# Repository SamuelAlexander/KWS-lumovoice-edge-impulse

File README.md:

# Lumo Voice

Lumo Voice is a keyword spotting (KWS) project utilizing the Arduino Nicla Voice platform, designed to control LED lighting. This repository includes:

- **Arduino Code**: Arduino code for the Nicla Voice.
- **KiCAD PCB Files**: Schematics and PCB design for the custom LED control PCB.
- **Manufacturing**: Gerber, drill, and SMD Bill of Materials

## Getting Started

1. **Firmware**: Upload the Arduino code to the Nicla Voice..
2. **Hardware**: Use the provided KiCAD files to manufacture the custom PCB.

## Usage

The device responds to voice commands "extinguish" and "illuminate" to control the lights. An "z_openset" category handles unrecognized commands.

## License

This project is licensed under the Apache 2.0 License - see the [LICENSE](LICENSE) file for details.

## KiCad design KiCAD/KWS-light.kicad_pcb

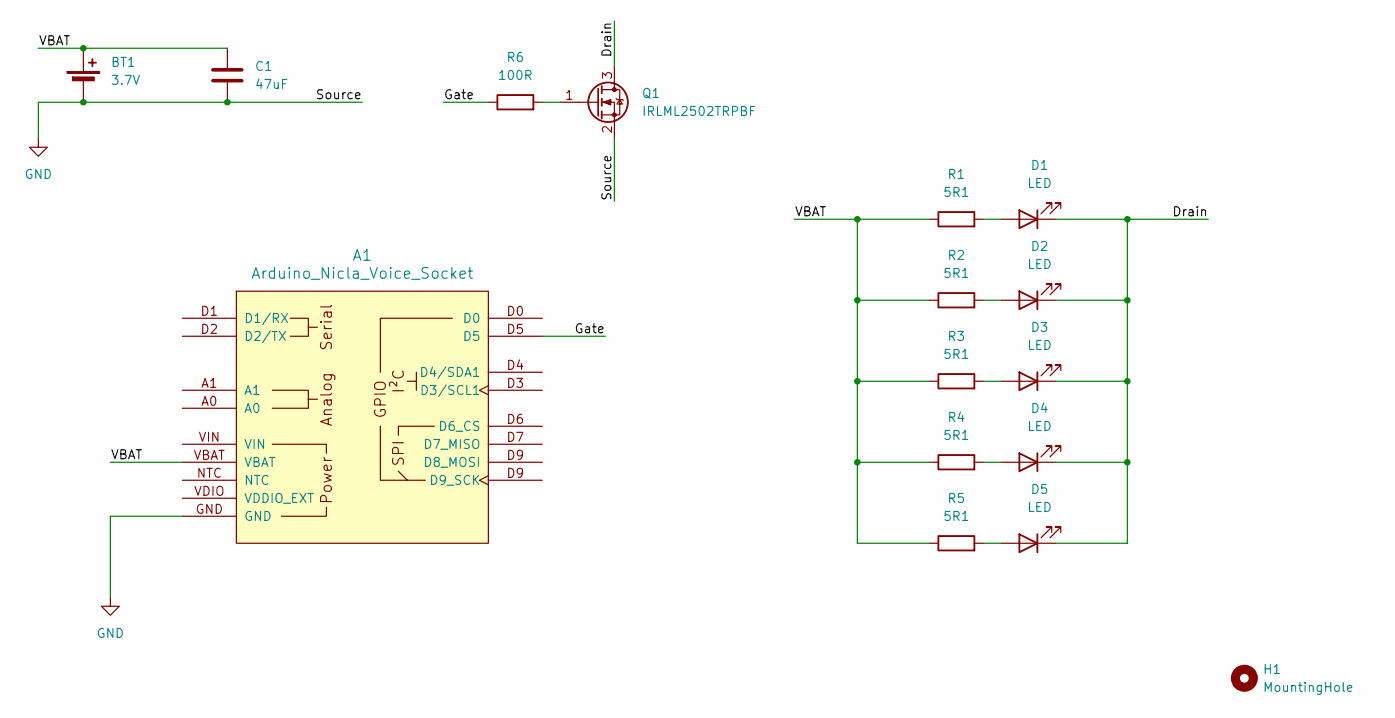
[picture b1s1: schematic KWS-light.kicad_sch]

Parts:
A1: Arduino_Nicla_Voice_Socket
BT1: 3.7V; PinSocket_1x02_P2.54mm_Vertical
C1: 47uF; C_1210_3225Metric; JLCPCB Part # C5440143
D1, D2, D3, D4, D5: LED; LED_PLCC_2835; JLCPCB Part # C516126
H1: MountingHole; MountingHole_3.2mm_M3
Q1: IRLML2502TRPBF; SOT-23; JLCPCB Part # C2589
R1, R2, R3, R4, R5: 5R1; R_1206_3216Metric; JLCPCB Part # C176224
R6: 100R; R_1206_3216Metric; JLCPCB Part # C176249

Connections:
/Drain: D1.1 (K), D2.1 (K), D3.1 (K), D4.1 (K), D5.1 (K), Q1.3 (D)
/Gate: A1.D5, R6.1
/VBAT: A1.VBAT, BT1.1 (+), C1.1, R1.1, R2.1, R3.1, R4.1, R5.1
GND: A1.GND, BT1.2 (-), C1.2, Q1.2 (S)
unnamed: D1.2 (A), R1.2
unnamed: D2.2 (A), R2.2
unnamed: D3.2 (A), R3.2
unnamed: D4.2 (A), R4.2
unnamed: D5.2 (A), R5.2
unnamed: Q1.1 (G), R6.2

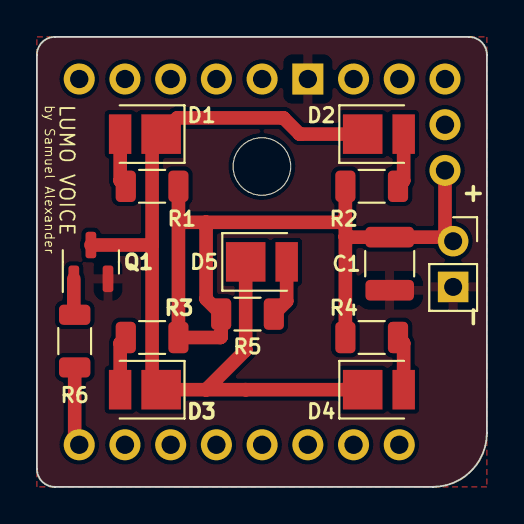
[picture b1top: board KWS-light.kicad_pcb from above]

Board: 2 copper layers, 25.0 x 25.0 mm, 16 parts (1 on the bottom side), 10 nets.
